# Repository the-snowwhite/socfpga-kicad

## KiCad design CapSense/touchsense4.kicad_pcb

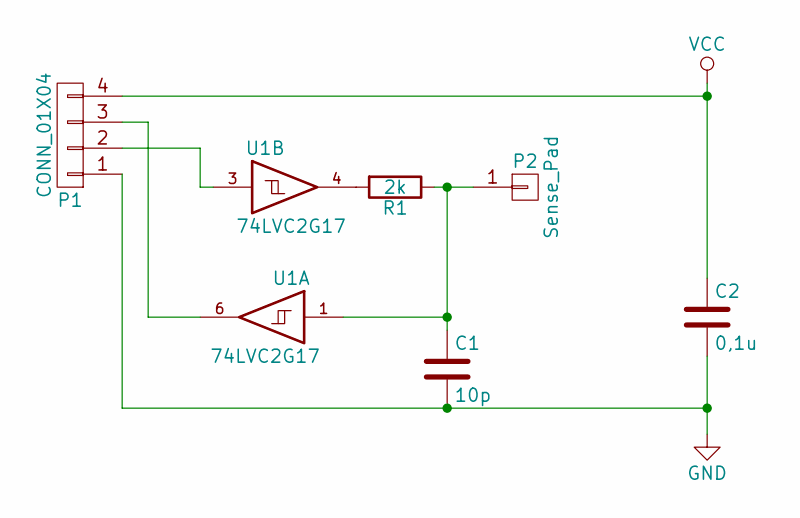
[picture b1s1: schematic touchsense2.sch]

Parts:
C1: 10p; C_1206
C2: 0,1u; C_1206
P1: CONN_01X04; Pin_Header_Straight_1x04_L
P2: Sense_Pad; 1pin_pad-round_s
R1: 2k; R_1206
U1: 74LVC2G17; SOT-23-6

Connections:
GND: C1.2, C2.2, P1.1, U1.2 (GND)
unnamed: C1.1, P2.1, R1.1, U1.1
unnamed: P1.2, U1.3
unnamed: P1.3, U1.6
unnamed: R1.2, U1.4
VCC: C2.1, P1.4, U1.5 (VCC)

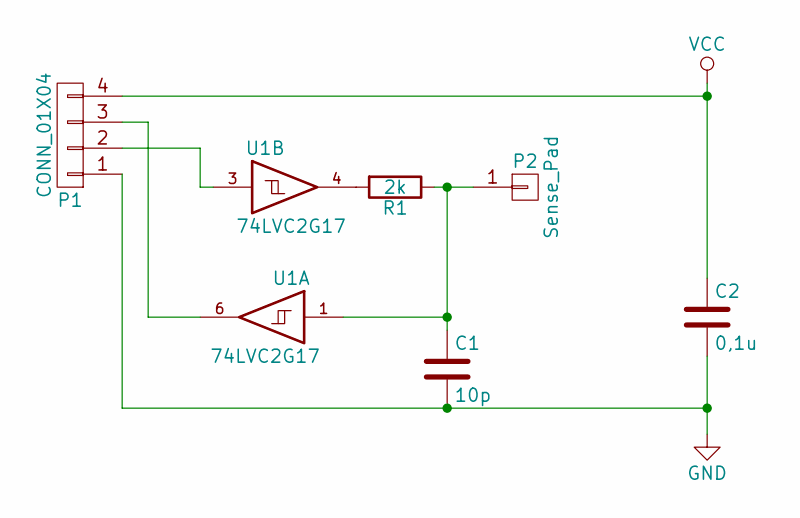
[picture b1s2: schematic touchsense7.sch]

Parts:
C1: 10p; C_1206_3216Metric
C2: 0,1u; C_1206_3216Metric
P1: CONN_01X04; PinHeader_1x04_P2.54mm_Vertical
P2: Sense_Pad; 1pin_pad-round_s
R1: 2k; R_1206_3216Metric
U1: 74LVC2G17; SOT-23-6

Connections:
GND: C1.2, C2.2, P1.1, U1.2 (GND)
unnamed: C1.1, P2.1, R1.1, U1.1
unnamed: P1.2, U1.3
unnamed: P1.3, U1.6
unnamed: R1.2, U1.4
VCC: C2.1, P1.4, U1.5 (VCC)

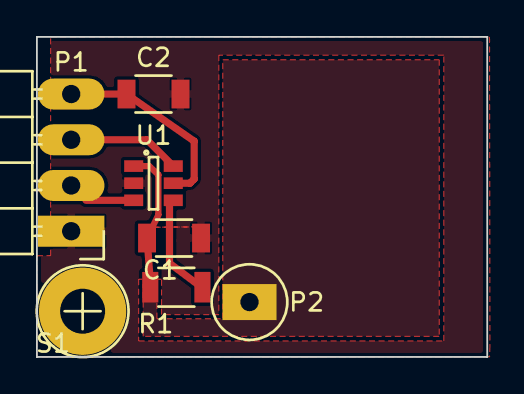
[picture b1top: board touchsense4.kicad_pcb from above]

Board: 2 copper layers, 25.0 x 17.8 mm, 7 parts (0 on the bottom side), 6 nets.

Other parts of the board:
S1: Screw; Screw_2.5mm

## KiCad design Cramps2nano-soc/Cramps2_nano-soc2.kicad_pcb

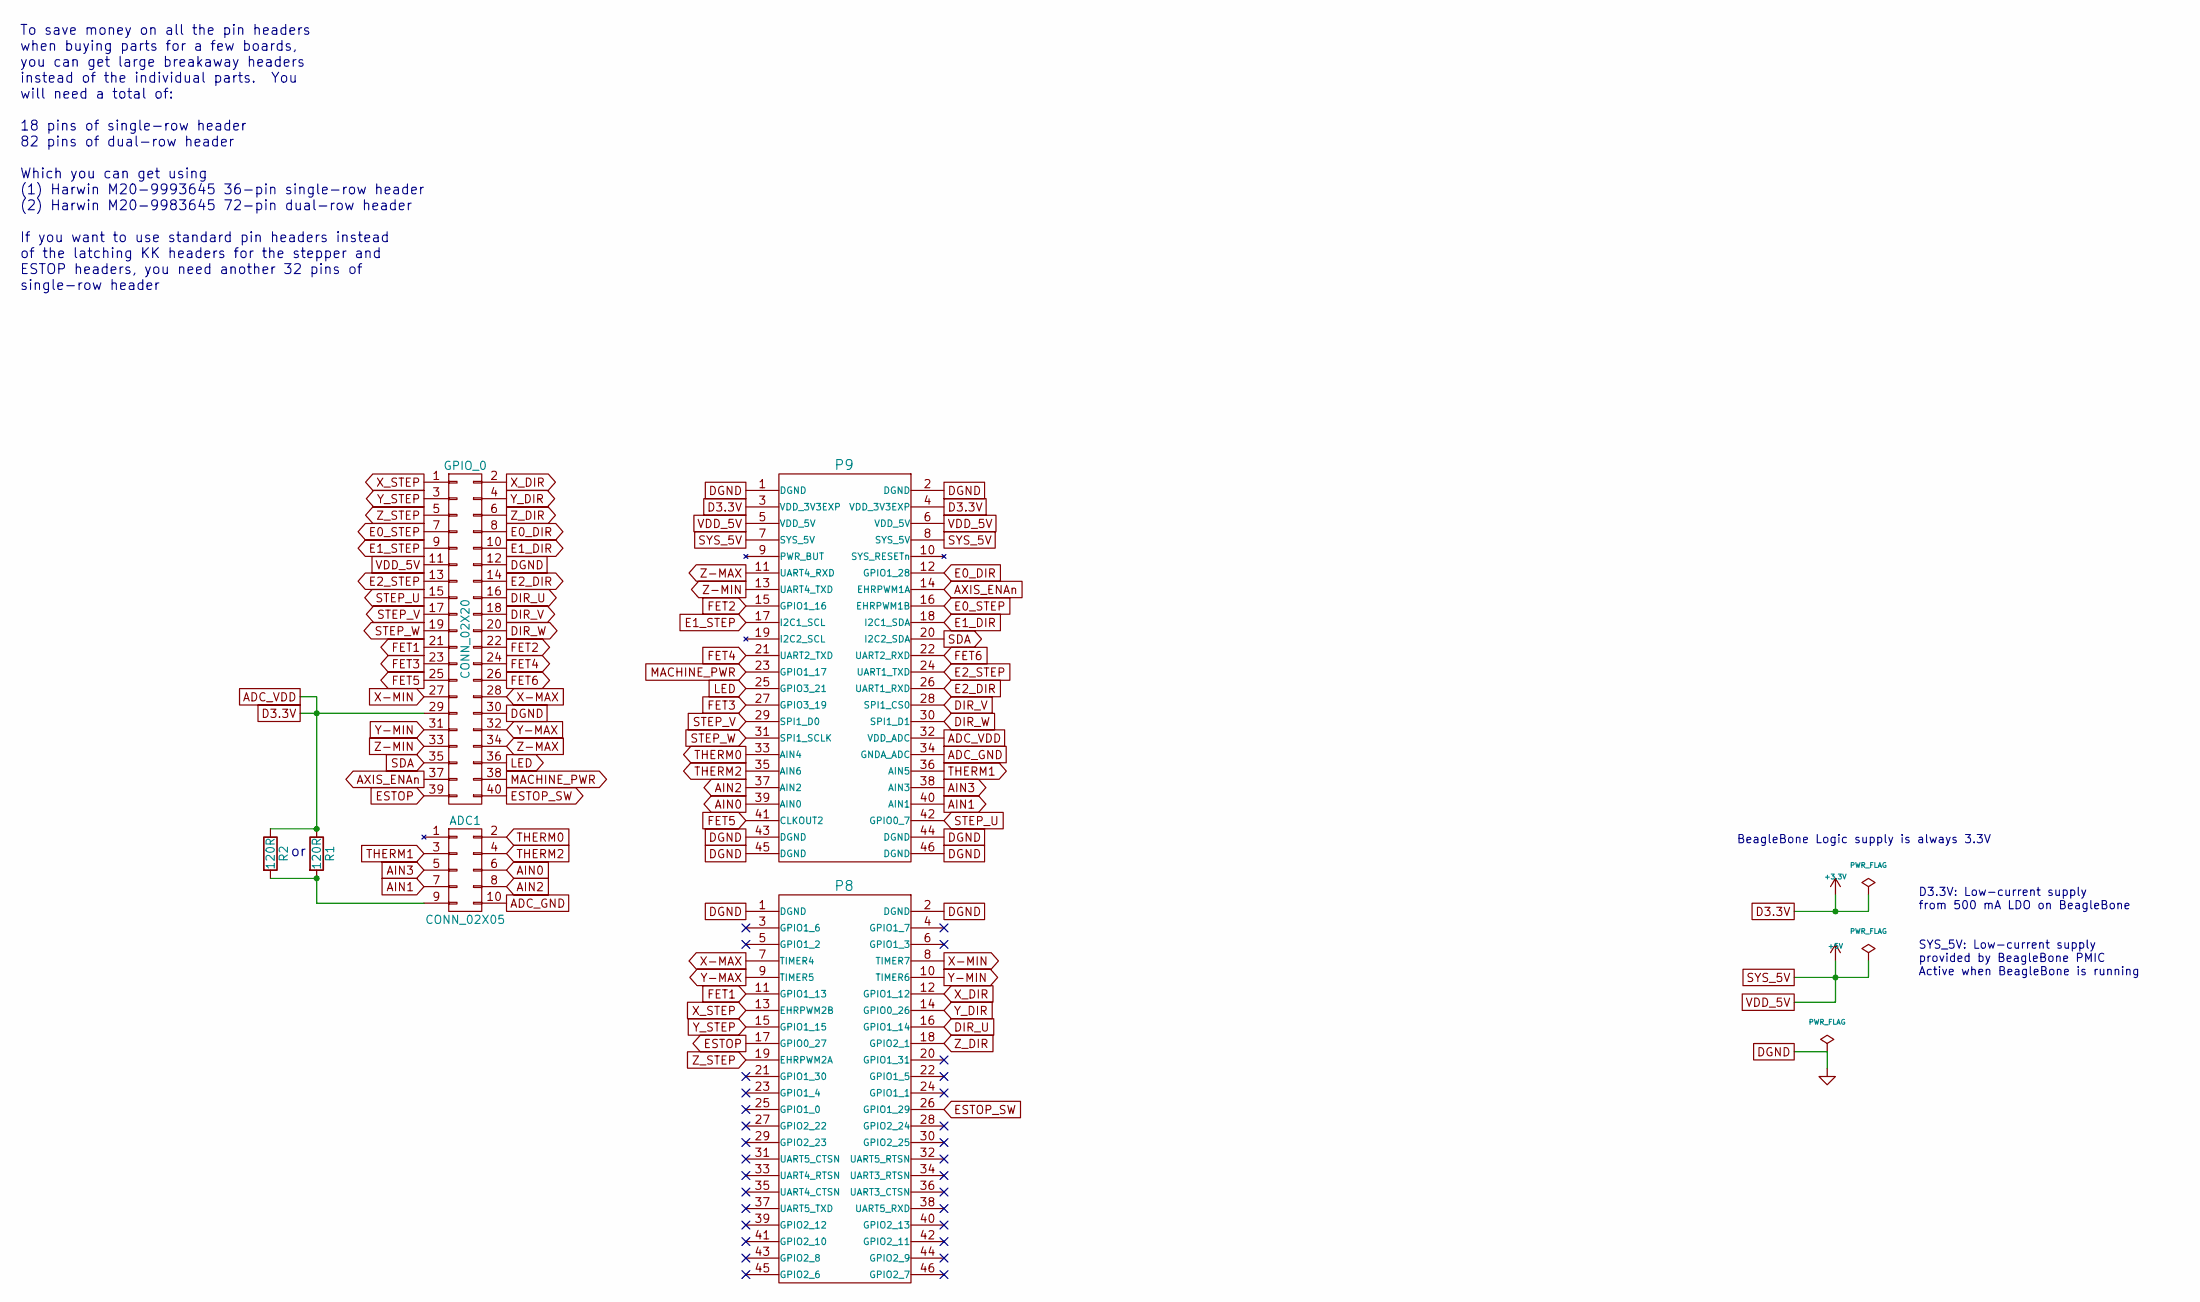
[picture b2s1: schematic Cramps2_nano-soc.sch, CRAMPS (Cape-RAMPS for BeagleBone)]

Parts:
ADC1: CONN_02X05; PinHeader_2x05_P2.54mm_Horizontal
GPIO_0: CONN_02X20; PinHeader_2x20_P2.54mm_Vertical
P8, P9: BB_EXP_CONN; PinHeader_2x23_P2.54mm_Vertical; PartNo TSHC-123-D-06-240-GT-LF
R1: 120R; R_Axial_DIN0207_L6.3mm_D2.5mm_P7.62mm_Horizontal
R2: 120R; R_1206_3216Metric_Pad1.42x1.75mm_HandSolder

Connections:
ADC_GND: ADC1.10, P9.34 (GNDA_ADC)
ADC_VDD: GPIO_0.29, P9.3 (VDD_3V3EXP), P9.4 (VDD_3V3EXP), P9.32 (VDD_ADC), R1.1, R2.1
AIN0: ADC1.6, P9.39 (AIN0)
AIN1: ADC1.7, P9.40 (AIN1)
AIN2: ADC1.8, P9.37 (AIN2)
AIN3: ADC1.5, P9.38 (AIN3)
AXIS_ENAn: GPIO_0.37, P9.14 (EHRPWM1A)
DGND: GPIO_0.12, GPIO_0.30, P8.1 (DGND), P8.2 (DGND), P9.1 (DGND), P9.2 (DGND), P9.43 (DGND), P9.44 (DGND), P9.45 (DGND), P9.46 (DGND)
DIR_U: GPIO_0.16, P8.16 (GPIO1_14)
DIR_V: GPIO_0.18, P9.28 (SPI1_CS0)
DIR_W: GPIO_0.20, P9.30 (SPI1_D1)
E0_DIR: GPIO_0.8, P9.12 (GPIO1_28)
E0_STEP: GPIO_0.7, P9.16 (EHRPWM1B)
E1_DIR: GPIO_0.10, P9.18 (I2C1_SDA)
E1_STEP: GPIO_0.9, P9.17 (I2C1_SCL)
E2_DIR: GPIO_0.14, P9.26 (UART1_RXD)
E2_STEP: GPIO_0.13, P9.24 (UART1_TXD)
ESTOP: GPIO_0.39, P8.17 (GPIO0_27)
ESTOP_SW: GPIO_0.40, P8.26 (GPIO1_29)
FET1: GPIO_0.21, P8.11 (GPIO1_13)
FET2: GPIO_0.22, P9.15 (GPIO1_16)
FET3: GPIO_0.23, P9.27 (GPIO3_19)
FET4: GPIO_0.24, P9.21 (UART2_TXD)
FET5: GPIO_0.25, P9.41 (CLKOUT2)
FET6: GPIO_0.26, P9.22 (UART2_RXD)
LED: GPIO_0.36, P9.25 (GPIO3_21)
MACHINE_PWR: GPIO_0.38, P9.23 (GPIO1_17)
unnamed: ADC1.9, R1.2, R2.2
SDA: GPIO_0.35, P9.20 (I2C2_SDA)
STEP_U: GPIO_0.15, P9.42 (GPIO0_7)
STEP_V: GPIO_0.17, P9.29 (SPI1_D0)
STEP_W: GPIO_0.19, P9.31 (SPI1_SCLK)
SYS_5V: GPIO_0.11, P9.5 (VDD_5V), P9.6 (VDD_5V), P9.7 (SYS_5V), P9.8 (SYS_5V)
THERM0: ADC1.2, P9.33 (AIN4)
THERM1: ADC1.3, P9.36 (AIN5)
THERM2: ADC1.4, P9.35 (AIN6)
X-MAX: GPIO_0.28, P8.7 (TIMER4)
X-MIN: GPIO_0.27, P8.8 (TIMER7)
X_DIR: GPIO_0.2, P8.12 (GPIO1_12)
X_STEP: GPIO_0.1, P8.13 (EHRPWM2B)
Y-MAX: GPIO_0.32, P8.9 (TIMER5)
Y-MIN: GPIO_0.31, P8.10 (TIMER6)
Y_DIR: GPIO_0.4, P8.14 (GPIO0_26)
Y_STEP: GPIO_0.3, P8.15 (GPIO1_15)
Z-MAX: GPIO_0.34, P9.11 (UART4_RXD)
Z-MIN: GPIO_0.33, P9.13 (UART4_TXD)
Z_DIR: GPIO_0.6, P8.18 (GPIO2_1)
Z_STEP: GPIO_0.5, P8.19 (EHRPWM2A)

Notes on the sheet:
To save money on all the pin headers when buying parts for a few boards, you can get large breakaway headers instead of the individual parts. You will need a total of: 18 pins of single-row header 82 pins of dual-row header Which you can get using (1) Harwin M20-9993645 36-pin single-row header (2)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
BeagleBone Logic supply is always 3.3V
SYS_5V: Low-current supply provided by BeagleBone PMIC Active when BeagleBone is running
D3.3V: Low-current supply from 500 mA LDO on BeagleBone

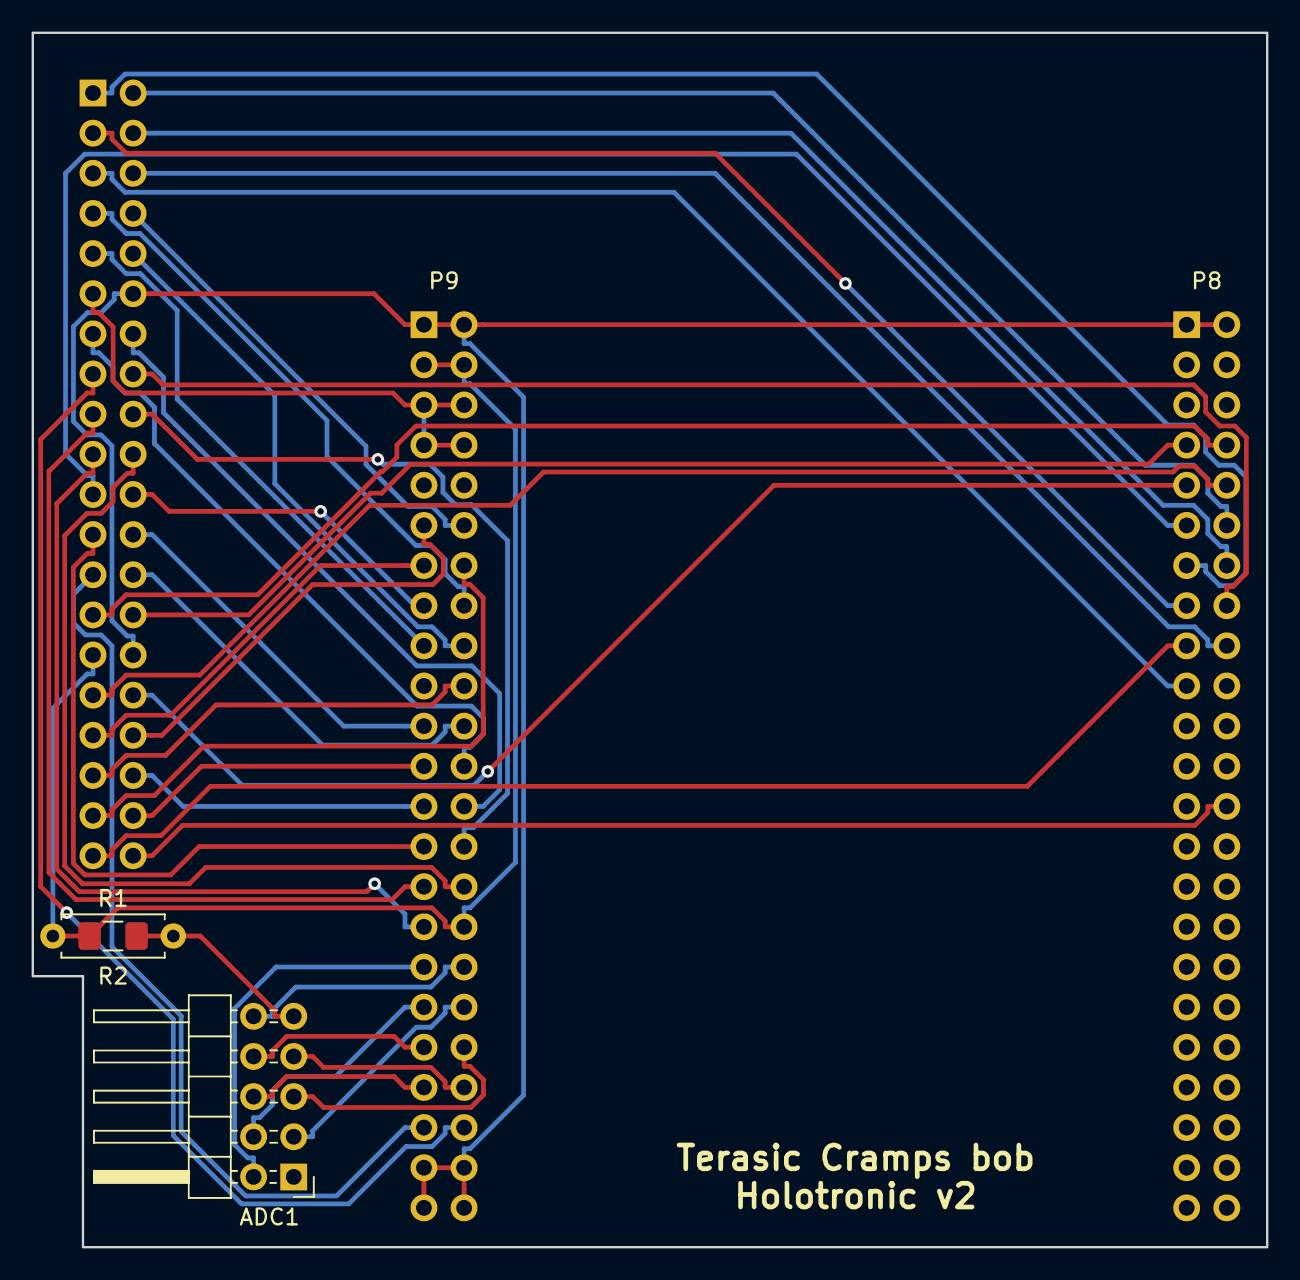
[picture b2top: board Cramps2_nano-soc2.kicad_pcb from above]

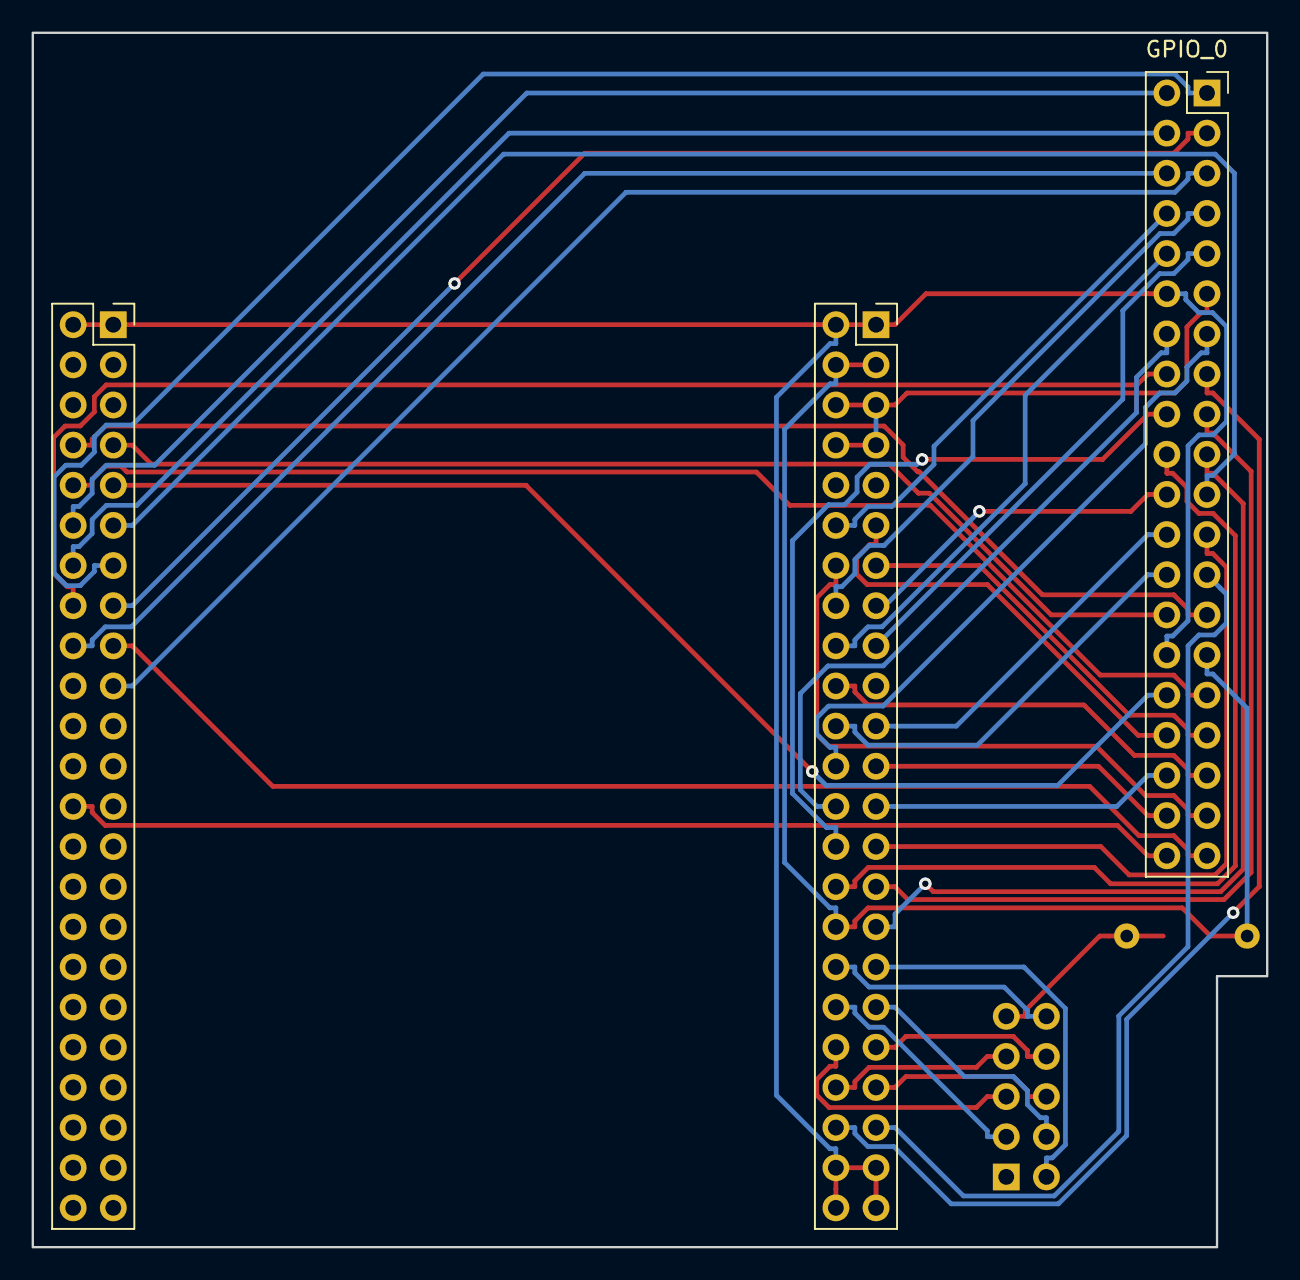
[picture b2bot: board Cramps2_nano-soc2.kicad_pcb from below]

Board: 2 copper layers, 78.1 x 76.8 mm, 6 parts (3 on the bottom side), 48 nets.

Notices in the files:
Cramps2nano-soc/Cramps2_nano-soc.sch:
Copyright 2014 GPL v3
